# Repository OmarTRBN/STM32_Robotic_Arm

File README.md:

# STM32_Robotic_Arm
Capstone project - STM32-controlled 4DOF robotic arm designed for trajectory tracking, controller comparison and system identification experiments.

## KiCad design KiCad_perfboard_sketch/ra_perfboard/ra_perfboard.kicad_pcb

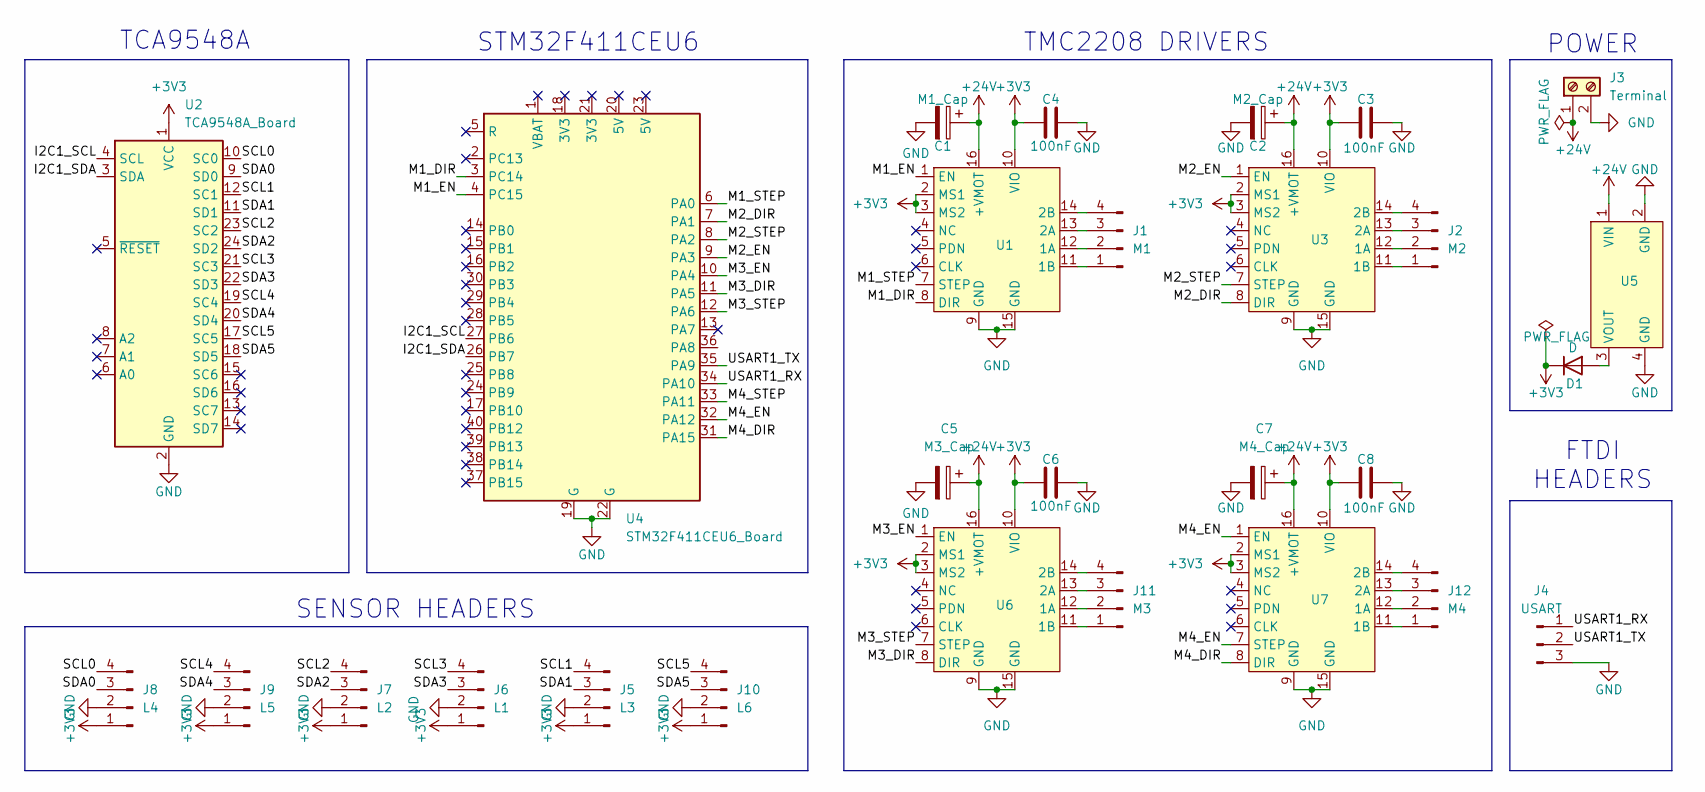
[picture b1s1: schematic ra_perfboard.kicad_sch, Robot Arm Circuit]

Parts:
C1: M1_Cap; CP_Radial_D5.0mm_P2.50mm
C2: M2_Cap; CP_Radial_D5.0mm_P2.50mm
C3, C4, C6, C8: 100nF; C_Disc_D3.0mm_W2.0mm_P2.50mm
C5: M3_Cap; CP_Radial_D5.0mm_P2.50mm
C7: M4_Cap; CP_Radial_D5.0mm_P2.50mm
D1: D; D_DO-15_P10.16mm_Horizontal
J1: M1; PinHeader_1x04_P2.54mm_Vertical
J2: M2; PinHeader_1x04_P2.54mm_Vertical
J3: Terminal; TerminalBlock_Phoenix_MKDS-1,5-2-5.08_1x02_P5.08mm_Horizont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
J4: USART; PinHeader_1x03_P2.54mm_Vertical
J5: L3; PinHeader_1x04_P2.54mm_Vertical
J6: L1; PinHeader_1x04_P2.54mm_Vertical
J7: L2; PinHeader_1x04_P2.54mm_Vertical
J8: L4; PinHeader_1x04_P2.54mm_Vertical
J9: L5; PinHeader_1x04_P2.54mm_Vertical
J10: L6; PinHeader_1x04_P2.54mm_Vertical
J11: M3; PinHeader_1x04_P2.54mm_Vertical
J12: M4; PinHeader_1x04_P2.54mm_Vertical
U1, U3, U6, U7: TMC2208_Board_Footprint
U2: TCA9548A_Board; TCA9548A_Board_Footprint
U4: STM32F411CEU6_Board
U5: LM2596_Board_BC_Footprint

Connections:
+3V3: C3.1, C4.1, C6.1, C8.1, D1.1 (K), J5.1, J6.1, J7.1, J8.1, J9.1, J10.1, U1.2 (MS1), U1.3 (MS2), U1.10 (VIO), U2.1 (VCC), U3.2 (MS1), U3.3 (MS2), U3.10 (VIO), U6.2 (MS1), U6.3 (MS2), U6.10 (VIO), U7.2 (MS1), U7.3 (MS2), U7.10 (VIO)
+24V: C1.1, C2.1, C5.1, C7.1, J3.1, U1.16 (+VMOT), U3.16 (+VMOT), U5.1 (VIN), U6.16 (+VMOT), U7.16 (+VMOT)
/I2C1_SCL: U2.4 (SCL), U4.27 (PB6)
/I2C1_SDA: U2.3 (SDA), U4.26 (PB7)
/M1_DIR: U1.8 (DIR), U4.3 (PC14)
/M1_EN: U1.1 (EN), U4.4 (PC15)
/M1_STEP: U1.7 (STEP), U4.6 (PA0)
/M2_DIR: U3.8 (DIR), U4.7 (PA1)
/M2_EN: U3.1 (EN), U4.9 (PA3)
/M2_STEP: U3.7 (STEP), U4.8 (PA2)
/M3_DIR: U4.11 (PA5), U6.8 (DIR)
/M3_EN: U4.10 (PA4), U6.1 (EN)
/M3_STEP: U4.12 (PA6), U6.7 (STEP)
/M4_DIR: U4.31 (PA15), U7.8 (DIR)
/M4_EN: U4.32 (PA12), U7.1 (EN), U7.7 (STEP)
/M4_STEP: U4.33 (PA11)
/SCL0: J8.4, U2.10 (SC0)
/SCL1: J5.4, U2.12 (SC1)
/SCL2: J7.4, U2.23 (SC2)
/SCL3: J6.4, U2.21 (SC3)
/SCL4: J9.4, U2.19 (SC4)
/SCL5: J10.4, U2.17 (SC5)
/SDA0: J8.3, U2.9 (SD0)
/SDA1: J5.3, U2.11 (SD1)
/SDA2: J7.3, U2.24 (SD2)
/SDA3: J6.3, U2.22 (SD3)
/SDA4: J9.3, U2.20 (SD4)
/SDA5: J10.3, U2.18 (SD5)
/USART1_RX: J4.1, U4.34 (PA10)
/USART1_TX: J4.2, U4.35 (PA9)
GND: C1.2, C2.2, C3.2, C4.2, C5.2, C6.2, C7.2, C8.2, J3.2, J4.3, J5.2, J6.2, J7.2, J8.2, J9.2, J10.2, U1.9 (GND), U1.15 (GND), U2.2 (GND), U3.9 (GND), U3.15 (GND), U4.19 (G), U4.22 (G), U5.2 (GND), U5.4 (GND), U6.9 (GND), U6.15 (GND), U7.9 (GND), U7.15 (GND)
unnamed: D1.2 (A), U5.3 (VOUT)
unnamed: J1.1, U1.11 (1B)
unnamed: J1.2, U1.12 (1A)
unnamed: J1.3, U1.13 (2A)
unnamed: J1.4, U1.14 (2B)
unnamed: J2.1, U3.11 (1B)
unnamed: J2.2, U3.12 (1A)
unnamed: J2.3, U3.13 (2A)
unnamed: J2.4, U3.14 (2B)
unnamed: J11.1, U6.11 (1B)
unnamed: J11.2, U6.12 (1A)
unnamed: J11.3, U6.13 (2A)
unnamed: J11.4, U6.14 (2B)
unnamed: J12.1, U7.11 (1B)
unnamed: J12.2, U7.12 (1A)
unnamed: J12.3, U7.13 (2A)
unnamed: J12.4, U7.14 (2B)

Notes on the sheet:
TCA9548A
POWER
TMC2208 DRIVERS
SENSOR HEADERS
STM32F411CEU6
FTDI HEADERS

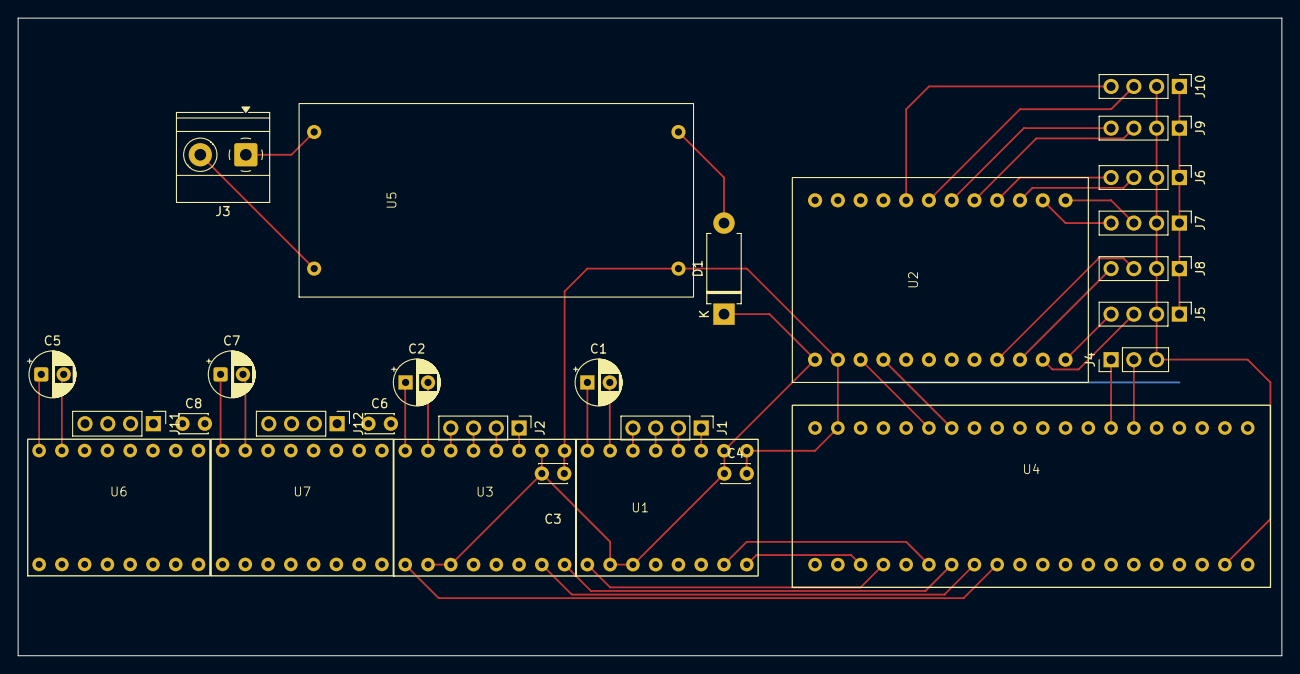
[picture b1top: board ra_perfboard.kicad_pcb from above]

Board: 2 copper layers, 141.0 x 71.1 mm, 28 parts (0 on the bottom side), 47 nets.

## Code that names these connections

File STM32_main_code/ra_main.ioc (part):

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Mcu.Name=STM32F411C(C-E)Ux
Mcu.Package=UFQFPN48
Mcu.UserName=STM32F411CEUx
PA0-WKUP.GPIOParameters=GPIO_ModeDefaultPP,GPIO_Speed,GPIO_PuPd
PA0-WKUP.GPIO_ModeDefaultPP=GPIO_MODE_AF_PP
PA0-WKUP.GPIO_PuPd=GPIO_NOPULL
PA0-WKUP.GPIO_Speed=GPIO_SPEED_FREQ_LOW
PA0-WKUP.Signal=S_TIM5_CH1
PA1.GPIOParameters=GPIO_Label
PA1.GPIO_Label=M2_DIR
PA1.Signal=GPIO_Output
PA10.Mode=Asynchronous
PA10.Signal=USART1_RX
PA11.Signal=S_TIM1_CH4
PA12.GPIOParameters=GPIO_Label
PA12.GPIO_Label=M4_EN
PA12.Signal=GPIO_Output
PA13.Mode=Serial_Wire
PA13.Signal=SYS_JTMS-SWDIO
PA14.Mode=Serial_Wire
PA14.Signal=SYS_JTCK-SWCLK
PA15.GPIOParameters=GPIO_Label
PA15.GPIO_Label=M4_DIR
PA15.Signal=GPIO_Output
PA2.GPIOParameters=GPIO_Speed,GPIO_PuPd
PA2.GPIO_PuPd=GPIO_PULLDOWN
PA2.GPIO_Speed=GPIO_SPEED_FREQ_HIGH
PA2.Signal=S_TIM9_CH1
PA3.GPIOParameters=GPIO_Label
PA3.GPIO_Label=M2_EN
PA3.Signal=GPIO_Output
PA4.GPIOParameters=GPIO_Label
PA4.GPIO_Label=M3_EN
PA4.Signal=GPIO_Output
PA5.GPIOParameters=GPIO_Label
PA5.GPIO_Label=M3_DIR
PA5.Signal=GPIO_Output
PA6.Signal=S_TIM3_CH1
PA9.Mode=Asynchronous
PA9.Signal=USART1_TX
PB6.GPIOParameters=GPIO_Pu
PB6.GPIO_Pu=GPIO_PULLUP
PB6.Mode=I2C
PB6.Signal=I2C1_SCL
PB7.GPIOParameters=GPIO_Pu
PB7.GPIO_Pu=GPIO_PULLUP
PB7.Mode=I2C
PB7.Signal=I2C1_SDA
PC13-ANTI_TAMP.GPIOParameters=GPIO_Label
PC13-ANTI_TAMP.GPIO_Label=TEST_LED
PC13-ANTI_TAMP.Signal=GPIO_Output
PC14-OSC32_IN.GPIOParameters=GPIO_Label
PC14-OSC32_IN.GPIO_Label=M1_DIR
PC14-OSC32_IN.Signal=GPIO_Output
PC15-OSC32_OUT.GPIOParameters=GPIO_PuPd,GPIO_Label
PC15-OSC32_OUT.GPIO_Label=M1_EN
PC15-OSC32_OUT.GPIO_PuPd=GPIO_PULLDOWN
PC15-OSC32_OUT.Signal=GPIO_Output
PH0\ -\ OSC_IN.Mode=HSE-External-Oscillator
PH0\ -\ OSC_IN.Signal=RCC_OSC_IN
PH1\ -\ OSC_OUT.Mode=HSE-External-Oscillator
PH1\ -\ OSC_OUT.Signal=RCC_OSC_OUT
RCC.HSE_VALUE=25000000
RCC.SYSCLKFreq_VALUE=100000000
RCC.SYSCLKSource=RCC_SYSCLKSOURCE_PLLCLK
board=custom

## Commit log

2025-03-04 Initial commit of STM32 Robotic Arm project.
2025-03-04 Added Multivariable PID library.
2025-03-04 Performed first test of Multivariable PID library.
2025-03-06 Added TMC2208 board symbol and footprint.
2025-03-06 Added STM32 board symbol and footprint.
2025-03-06 Added TCA9548A and LM3596 boards to perfboard layout.
2025-03-08 Configured pins in .ioc file and worked on KiCad perfboard.
2025-03-10 Updated commands to be use 2 bytes instead of 1, and made modifications on perfboard and pins.
2025-03-17 Removed bug in LUT set speed function. Updates to MATLAB GUI and KiCad perfboard. Successfully tested TCA9548A library.
2025-03-20 Added buttons in GUI to enable/disable motors along with STM32 functions to handle them.
2025-03-20 Added PID parameter parsing functions.
2025-03-24 Worked on trajectory generation in MATLAB.
2025-03-27 Added plotting and animating trajectory functions in MATLAB.
2025-03-30 Added trajectory button layout to MATLAB GUI.
2025-04-02 Added trajectory coefficients parsing functions.
2025-05-11 Modified AS5600_Mux library and added DMA functionality.
2025-05-15 Tested new AS5600_Mux library with FreeRTOS.
2025-05-22 Added modular SerialComm library to replace CommandProtocol.
2025-05-22 Fixed bug in controller parameters parsing function.
2025-06-05 Updated README with project scope
2025-06-18 Added Mutex for UART communication for simultaneous data reception and transmission.
2025-06-20 Added sliders for manual joint setpoint control to the MATLAB GUI.
2025-06-22 Organized STM32 project files, tested all 4 AS5600 modules successfully.
2025-07-10 Final commit after submitting project. Currently no plans to proegress in this project any further.
